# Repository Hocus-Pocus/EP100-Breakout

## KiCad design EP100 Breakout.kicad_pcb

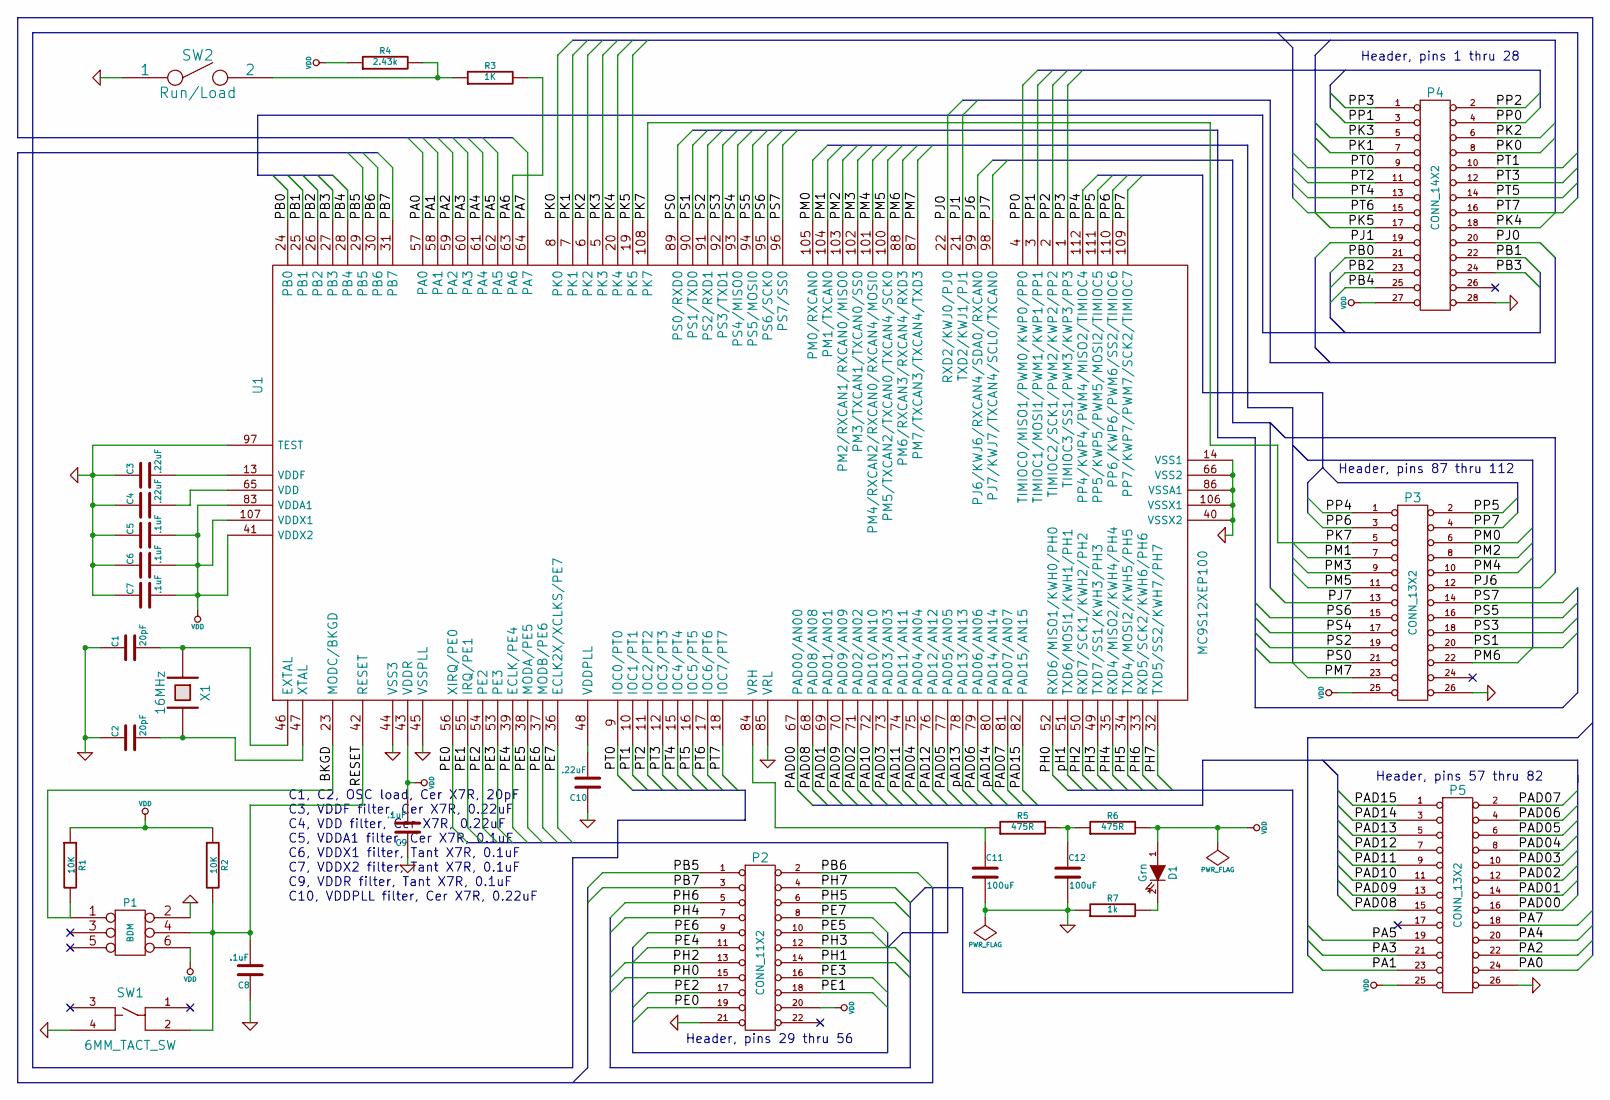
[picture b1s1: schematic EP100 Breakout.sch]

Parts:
C1, C2: 20pF
C3, C4, C10: .22uF
C5, C6, C7, C8, C9: .1uF
C11, C12: 100uF
D1: Grn
P1: BDM
P2: CONN_11X2
P3, P5: CONN_13X2
P4: CONN_14X2
R1, R2: 10K
R3: 1K
R4: 2.43k
R5, R6: 475R
R7: 1k
SW1: 6MM_TACT_SW
SW2: Run/Load
U1: MC9S12XEP100
X1: 16MHz

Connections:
/BKGD: P1.1, R1.2, U1.23 (MODC/BKGD)
/PA0: P5.24 (P20), U1.57 (PA0)
/PA1: P5.23, U1.58 (PA1)
/PA2: P5.22, U1.59 (PA2)
/PA3: P5.21, U1.60 (PA3)
/PA4: P5.20, U1.61 (PA4)
/PA5: P5.19, U1.62 (PA5)
/PA6: R3.2, U1.63 (PA6)
/PA7: P5.18, U1.64 (PA7)
/PAD00: P5.16, U1.67 (PAD00/AN00)
/PAD01: P5.14, U1.69 (PAD01/AN01)
/PAD02: P5.12, U1.71 (PAD02/AN02)
/PAD03: P5.10, U1.73 (PAD03/AN03)
/PAD04: P5.8, U1.75 (PAD04/AN04)
/PAD05: P5.6, U1.77 (PAD05/AN05)
/PAD06: P5.4, U1.79 (PAD06/AN06)
/PAD07: P5.2, U1.81 (PAD07/AN07)
/PAD08: P5.15, U1.68 (PAD08/AN08)
/PAD09: P5.13, U1.70 (PAD09/AN09)
/PAD10: P5.11, U1.72 (PAD10/AN10)
/PAD11: P5.9, U1.74 (PAD11/AN11)
/PAD12: P5.7, U1.76 (PAD12/AN12)
/PAD13: P5.5, U1.78 (PAD13/AN13)
/PAD14: P5.3, U1.80 (PAD14/AN14)
/PAD15: P5.1, U1.82 (PAD15/AN15)
/PB0: P4.21, U1.24 (PB0)
/PB1: P4.22, U1.25 (PB1)
/PB2: P4.23, U1.26 (PB2)
/PB3: P4.24 (P20), U1.27 (PB3)
/PB4: P4.25, U1.28 (PB4)
/PB5: P2.1, U1.29 (PB5)
/PB6: P2.2, U1.30 (PB6)
/PB7: P2.3, U1.31 (PB7)
/PE0: P2.19, U1.56 (XIRQ/PE0)
/PE1: P2.18, U1.55 (IRQ/PE1)
/PE2: P2.17, U1.54 (PE2)
/PE3: P2.16, U1.53 (PE3)
/PE4: P2.11, U1.39 (ECLK/PE4)
/PE5: P2.10, U1.38 (MODA/PE5)
/PE6: P2.9, U1.37 (MODB/PE6)
/PE7: P2.8, U1.36 (ECLK2X/XCLKS/PE7)
/PH0: P2.15, U1.52 (RXD6/MISO1/KWH0/PH0)
/PH1: P2.14, U1.51 (TXD6/MOSI1/KWH1/PH1)
/PH2: P2.13, U1.50 (RXD7/SCK1/KWH2/PH2)
/PH3: P2.12, U1.49 (TXD7/SS1/KWH3/PH3)
/PH4: P2.7, U1.35 (RXD4/MISO2/KWH4/PH4)
/PH5: P2.6, U1.34 (TXD4/MOSI2/KWH5/PH5)
/PH6: P2.5, U1.33 (RXD5/SCK2/KWH6/PH6)
/PH7: P2.4, U1.32 (TXD5/SS2/KWH7/PH7)
/PJ0: P4.20, U1.22 (RXD2/KWJ0/PJ0)
/PJ1: P4.19, U1.21 (TXD2/KWJ1/PJ1)
/PJ6: P3.12, U1.99 (PJ6/KWJ6/RXCAN4/SDA0/RXCAN0)
/PJ7: P3.13, U1.98 (PJ7/KWJ7/TXCAN4/SCL0/TXCAN0)
/PK0: P4.8, U1.8 (PK0)
/PK1: P4.7, U1.7 (PK1)
/PK2: P4.6, U1.6 (PK2)
/PK3: P4.5, U1.5 (PK3)
/PK4: P4.18, U1.20 (PK4)
/PK5: P4.17, U1.19 (PK5)
/PK7: P3.5, U1.108 (PK7)
/PM0: P3.6, U1.105 (PM0/RXCAN0)
/PM1: P3.7, U1.104 (PM1/TXCAN0)
/PM2: P3.8, U1.103 (PM2/RXCAN1/RXCAN0/MISO0)
/PM3: P3.9, U1.102 (PM3/TXCAN1/TXCAN0/SS0)
/PM4: P3.10, U1.101 (PM4/RXCAN2/RXCAN0/RXCAN4/MOSI0)
/PM5: P3.11, U1.100 (PM5/TXCAN2/TXCAN0/TXCAN4/SCK0)
/PM6: P3.22, U1.88 (PM6/RXCAN3/RXCAN4/RXD3)
/PM7: P3.23, U1.87 (PM7/TXCAN3/TXCAN4/TXD3)
/PP0: P4.4, U1.4 (TIMIOC0/MISO1/PWM0/KWP0/PP0)
/PP1: P4.3, U1.3 (TIMIOC1/MOSI1/PWM1/KWP1/PP1)
/PP2: P4.2, U1.2 (TIMIOC2/SCK1/PWM2/KWP2/PP2)
/PP3: P4.1, U1.1 (TIMIOC3/SS1/PWM3/KWP3/PP3)
/PP4: P3.1, U1.112 (PP4/KWP4/PWM4/MISO2/TIMIOC4)
/PP5: P3.2, U1.111 (PP5/KWP5/PWM5/MOSI2/TIMIOC5)
/PP6: P3.3, U1.110 (PP6/KWP6/PWM6/SS2/TIMIOC6)
/PP7: P3.4, U1.109 (PP7/KWP7/PWM7/SCK2/TIMIOC7)
/PS0: P3.21, U1.89 (PS0/RXD0)
/PS1: P3.20, U1.90 (PS1/TXD0)
/PS2: P3.19, U1.91 (PS2/RXD1)
/PS3: P3.18, U1.92 (PS3/TXD1)
/PS4: P3.17, U1.93 (PS4/MISO0)
/PS5: P3.16, U1.94 (PS5/MOSI0)
/PS6: P3.15, U1.95 (PS6/SCK0)
/PS7: P3.14, U1.96 (PS7/SS0)
/PT0: P4.9, U1.9 (IOC0/PT0)
/PT1: P4.10, U1.10 (IOC1/PT1)
/PT2: P4.11, U1.11 (IOC2/PT2)
/PT3: P4.12, U1.12 (IOC3/PT3)
/PT4: P4.13, U1.15 (IOC4/PT4)
/PT5: P4.14, U1.16 (IOC5/PT5)
/PT6: P4.15, U1.17 (IOC6/PT6)
/PT7: P4.16, U1.18 (IOC7/PT7)
/RESET: C8.2, P1.4, R2.2, SW1.2, U1.42 (RESET)
GND: C1.1, C2.1, C3.1, C4.1, C5.1, C6.1, C7.1, C8.1, C9.1, C10.1, C11.2, C12.2, P1.2, P2.21, P3.26, P4.28, P5.26, R7.1, SW1.4, SW2.1, U1.14 (VSS1), U1.40 (VSSX2), U1.44 (VSS3), U1.45 (VSSPLL), U1.66 (VSS2), U1.85 (VRL), U1.86 (VSSA1), U1.97 (TEST), U1.106 (VSSX1)
unnamed: C3.2, U1.13 (VDDF)
unnamed: C4.2, U1.65 (VDD)
unnamed: R3.1, R4.2, SW2.2
unnamed: C10.2, U1.48 (VDDPLL)
unnamed: C12.1, R5.2, R6.1
unnamed: C11.1, R5.1, U1.84 (VRH)
unnamed: D1.2 (K), R7.2
unnamed: C1.2, U1.46 (EXTAL), X1.1
unnamed: C2.2, U1.47 (XTAL), X1.2
VDD: C5.2, C6.2, C7.2, C9.2, D1.1 (A), P1.6, P2.20, P3.25, P4.27, P5.25, R1.1, R2.1, R4.1, R6.2, U1.41 (VDDX2), U1.43 (VDDR), U1.83 (VDDA1), U1.107 (VDDX1)

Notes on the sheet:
C1, C2, OSC load, Cer X7R, 20pF C3, VDDF filter, Cer X7R, 0.22uF C4, VDD filter, Cer X7R, 0.22uF C5, VDDA1 filter, Cer X7R, 0.1uF C6, VDDX1 filter, Tant X7R, 0.1uF C7, VDDX2 filter, Tant X7R, 0.1uF C9, VDDR filter, Tant X7R, 0.1uF C10, VDDPLL filter, Cer X7R, 0.22uF
Header, pins 29 thru 56
Header, pins 57 thru 82
Header, pins 87 thru 112
Header, pins 1 thru 28

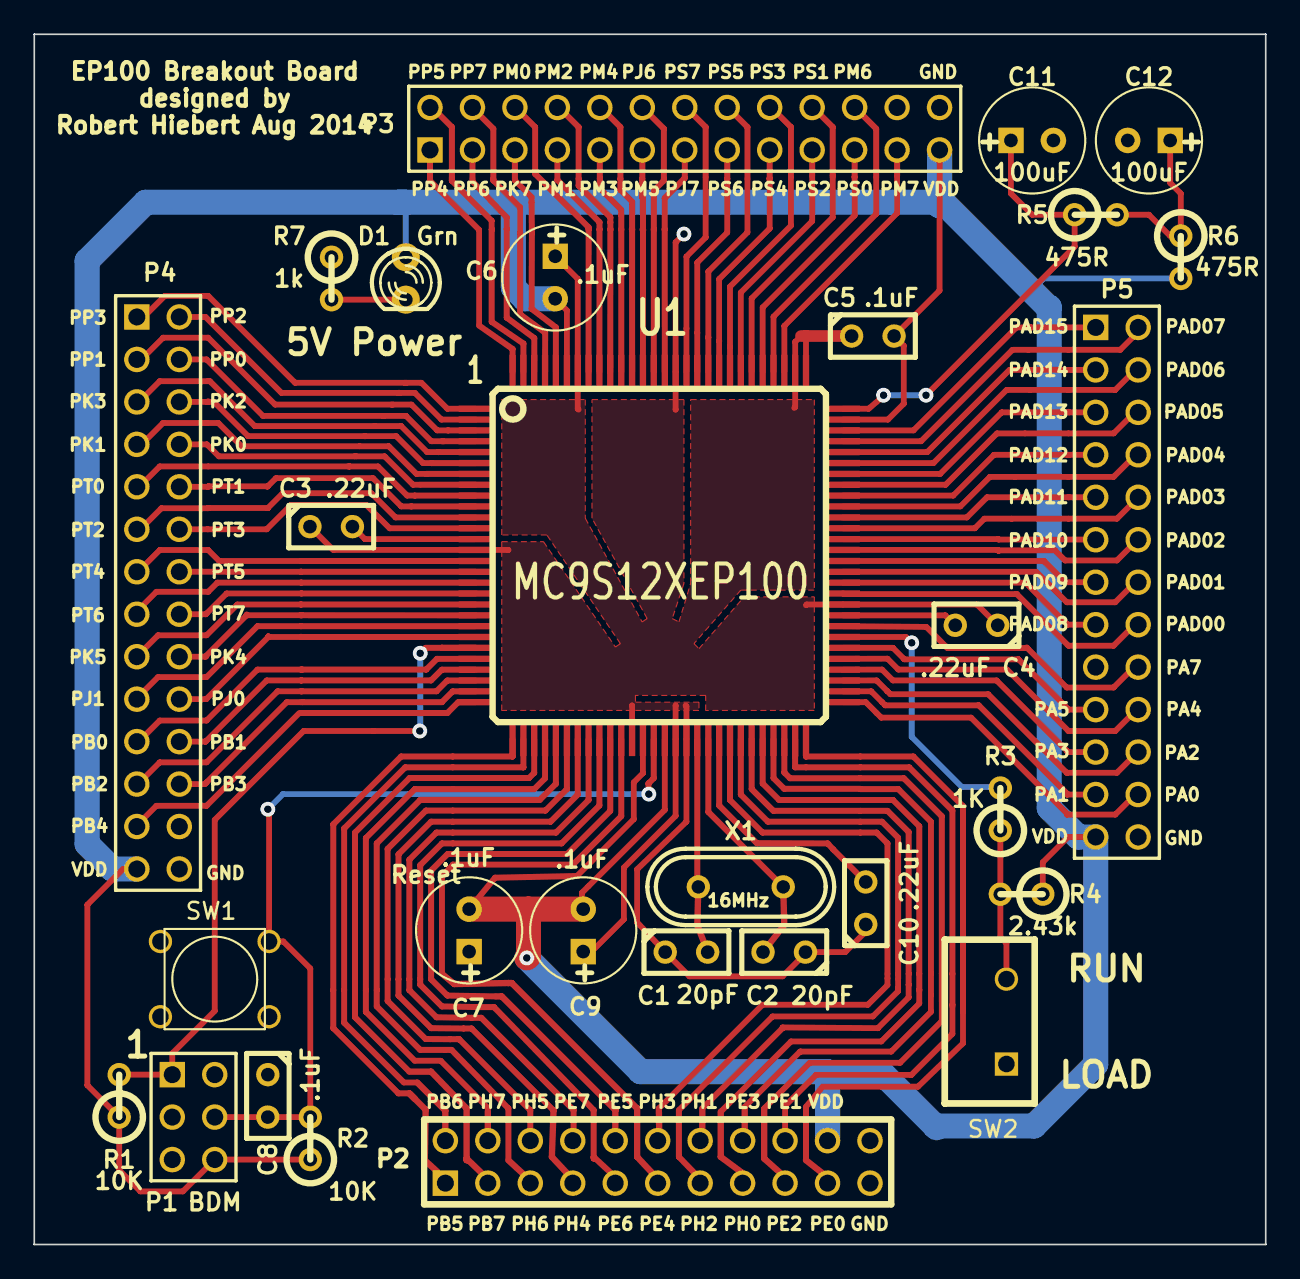
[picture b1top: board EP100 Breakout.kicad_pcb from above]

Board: 2 copper layers, 73.7 x 72.4 mm, 29 parts (0 on the bottom side), 104 nets.
